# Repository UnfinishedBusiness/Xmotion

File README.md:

# PlasmaTable
CNC Plasma Cutting Table Controls

Build SDL2-2.0.4 with ./configure --disable-video-mir --disable-video-wayland --disable-video-opengl --disable-video-x11 --host=armv7l-raspberry-linux-gnueabihf

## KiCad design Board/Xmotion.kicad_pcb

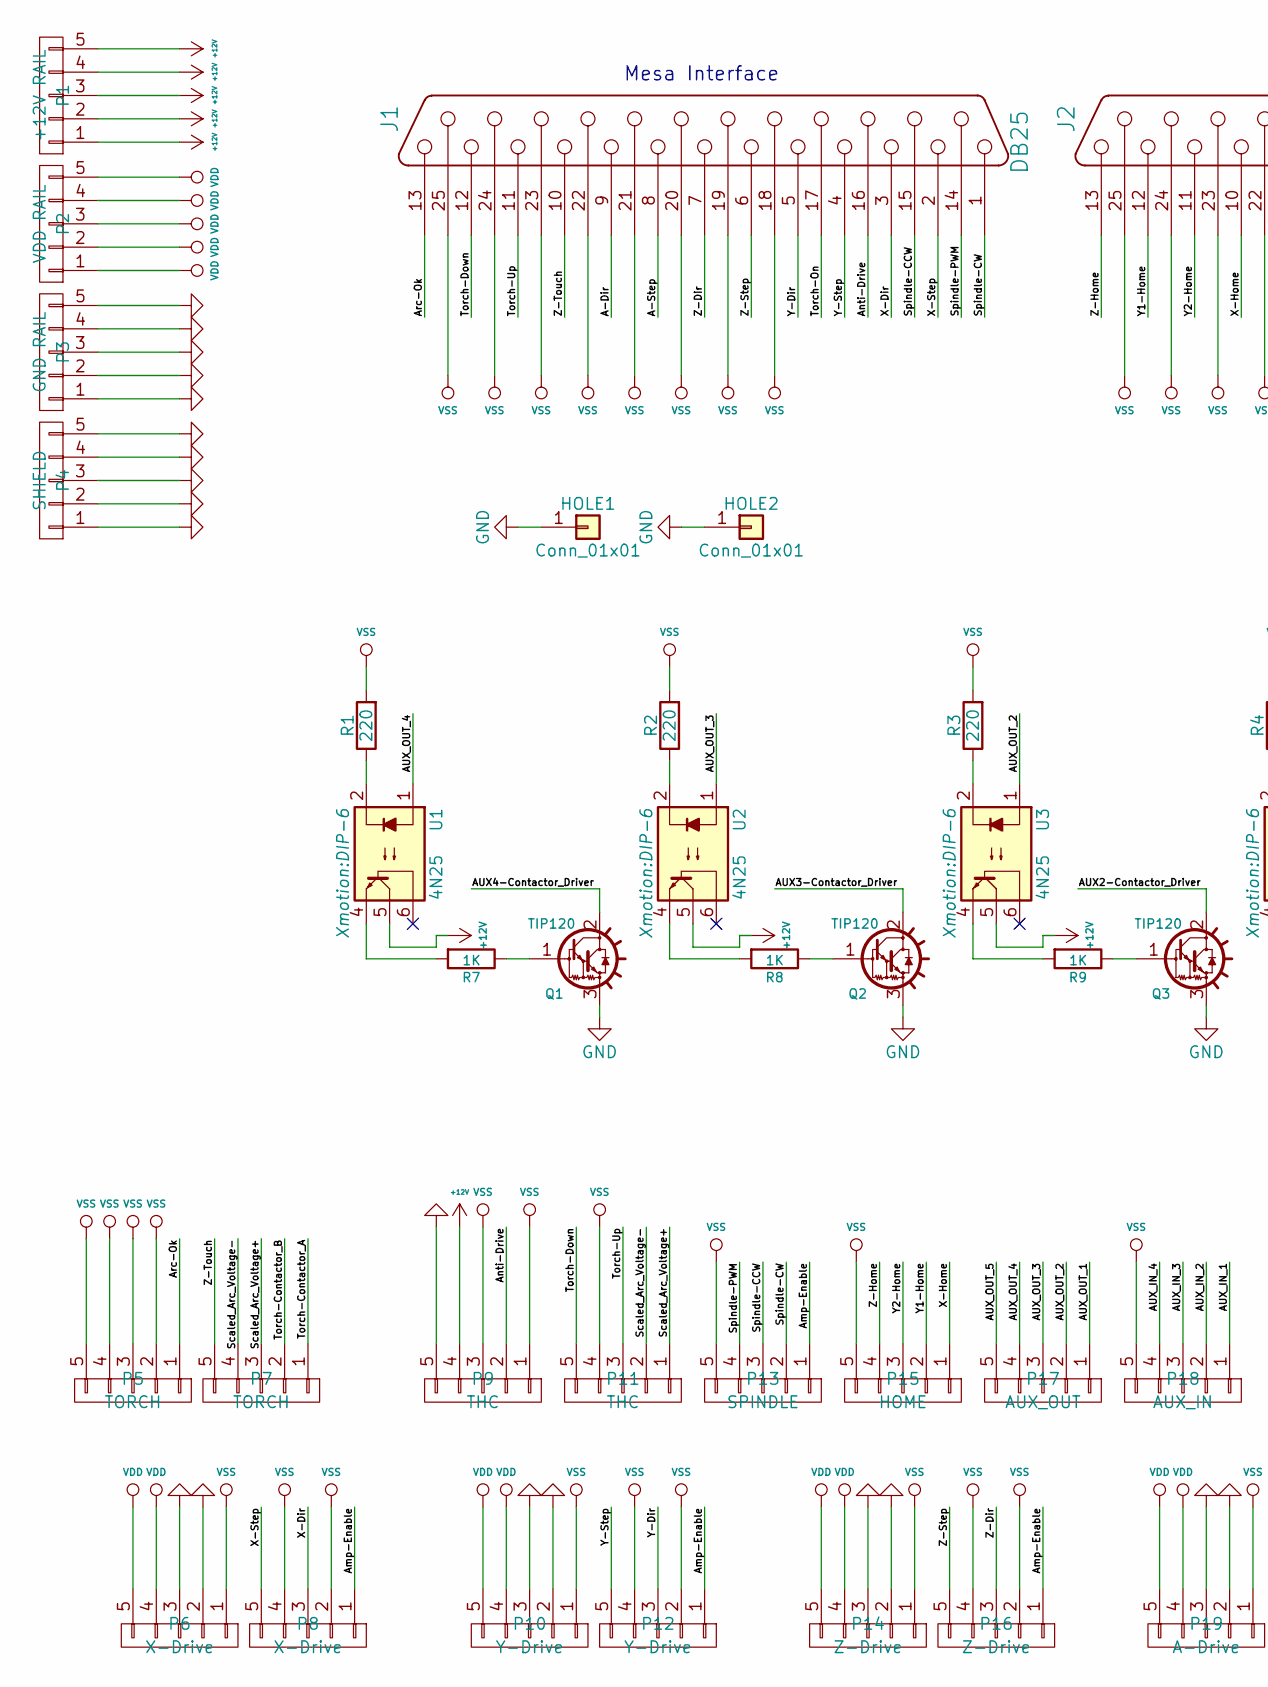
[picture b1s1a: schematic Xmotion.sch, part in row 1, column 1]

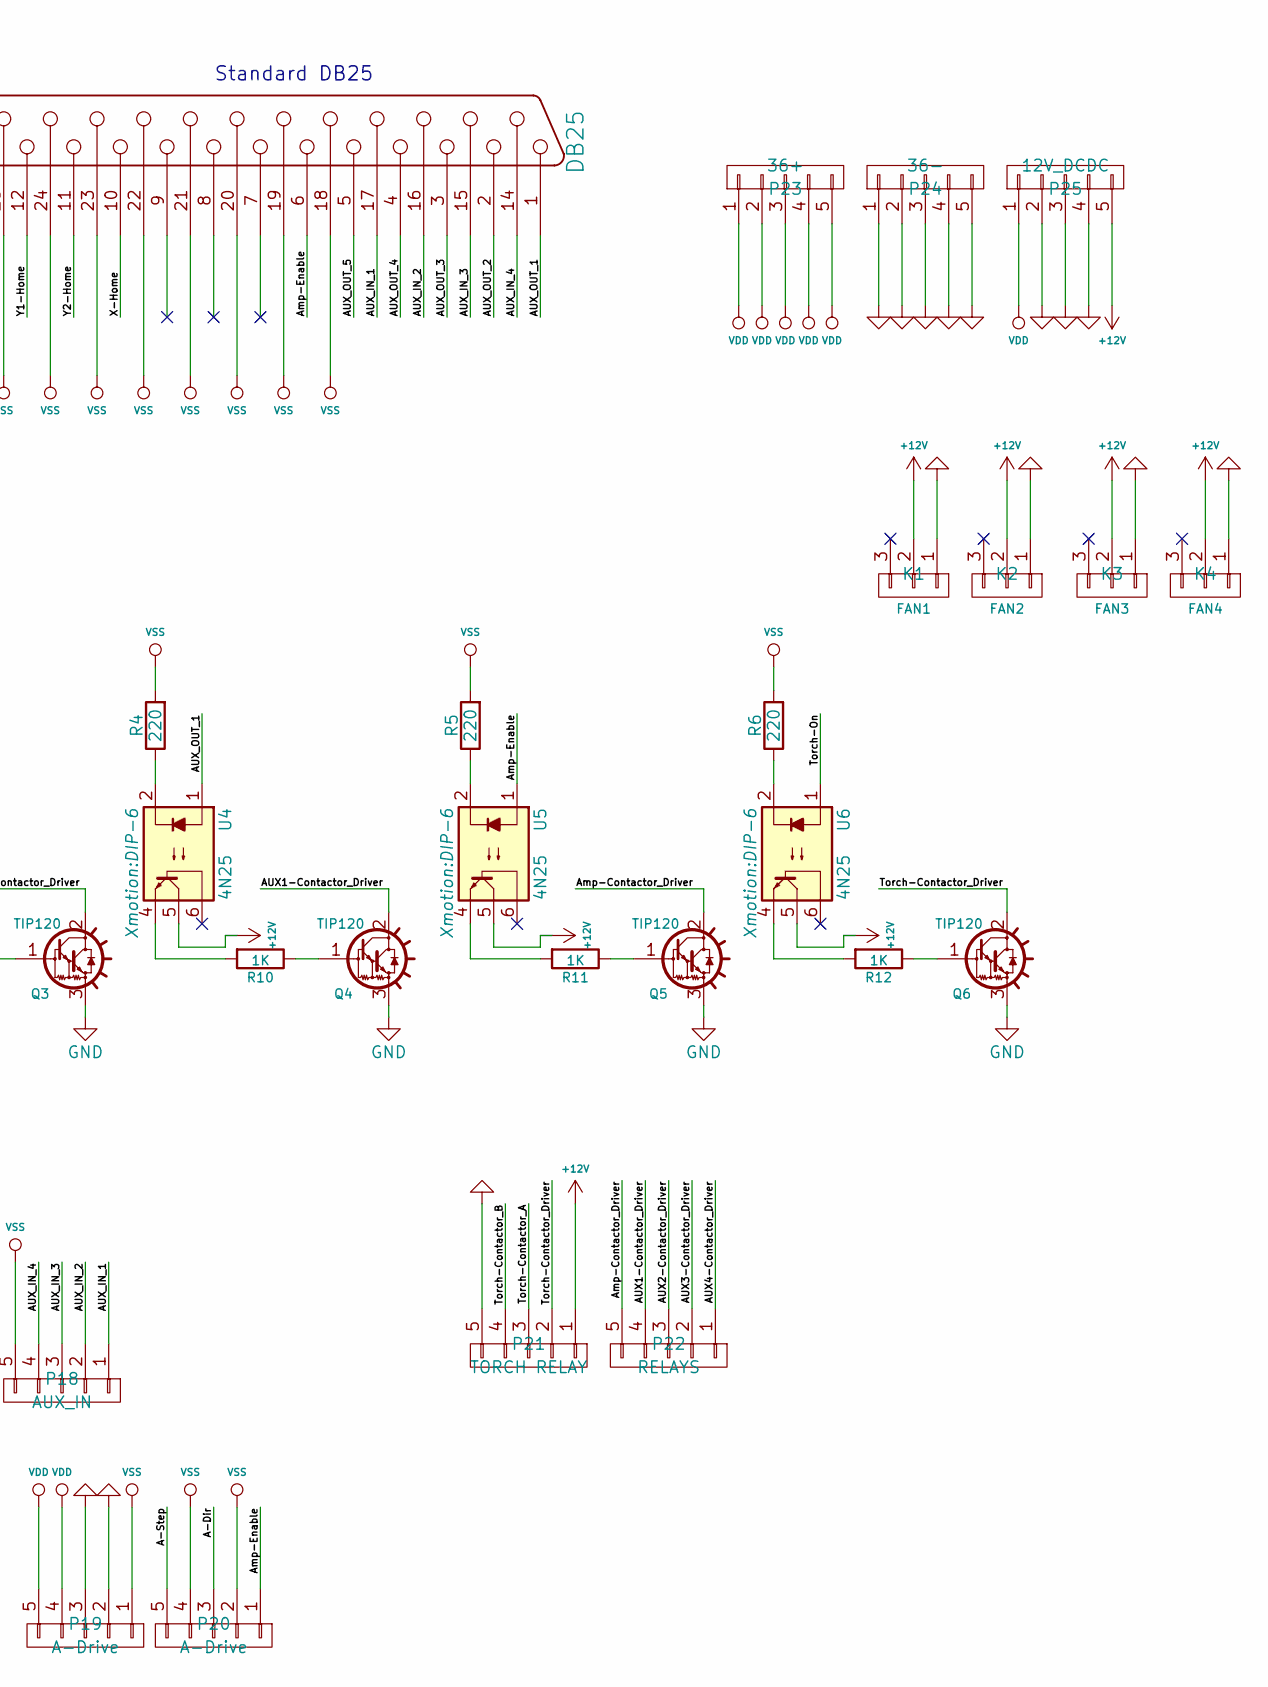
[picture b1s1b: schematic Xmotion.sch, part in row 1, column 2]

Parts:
HOLE1, HOLE2: Conn_01x01; BOLT_HOLE
J1, J2: DB25; DB25MC
K1: FAN1; SIL-3
K2: FAN2; SIL-3
K3: FAN3; SIL-3
K4: FAN4; SIL-3
P1: +12V RAIL; PLUGABLE_HEADER
P2: VDD RAIL; PLUGABLE_HEADER
P3: GND RAIL; PLUGABLE_HEADER
P4: SHIELD; PLUGABLE_HEADER
P5, P7: TORCH; PLUGABLE_HEADER
P6, P8: X-Drive; PLUGABLE_HEADER
P9, P11: THC; PLUGABLE_HEADER
P10, P12: Y-Drive; PLUGABLE_HEADER
P13: SPINDLE; PLUGABLE_HEADER
P14, P16: Z-Drive; PLUGABLE_HEADER
P15: HOME; PLUGABLE_HEADER
P17: AUX_OUT; PLUGABLE_HEADER
P18: AUX_IN; PLUGABLE_HEADER
P19, P20: A-Drive; PLUGABLE_HEADER
P21: TORCH RELAY; PLUGABLE_HEADER
P22: RELAYS; PLUGABLE_HEADER
P23: 36+; PLUGABLE_HEADER
P24: 36-; PLUGABLE_HEADER
P25: 12V_DCDC; PLUGABLE_HEADER
Q1, Q2, Q3, Q4, Q5, Q6: TIP120; TO220
R1, R2, R3, R4, R5, R6: 220; R3
R7, R8, R9, R10, R11, R12: 1K; R3
U1, U2, U3, U4, U5, U6: 4N25; DIP-6

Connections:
+12V: K1.2, K2.2, K3.2, K4.2, P1.1, P1.2, P1.3, P1.4, P1.5, P9.4, P21.1, P25.5, U1.5, U2.5, U3.5, U4.5, U5.5, U6.5
/A-Dir: J1.9, P20.3
/A-Step: J1.8, P20.5
/AUX1-Contactor_Driver: P22.4, Q4.2 (C)
/AUX2-Contactor_Driver: P22.3, Q3.2 (C)
/AUX3-Contactor_Driver: P22.2, Q2.2 (C)
/AUX4-Contactor_Driver: P22.1, Q1.2 (C)
/AUX_IN_1: J2.17, P18.1
/AUX_IN_2: J2.16, P18.2
/AUX_IN_3: J2.15, P18.3
/AUX_IN_4: J2.14, P18.4
/AUX_OUT_1: J2.1, P17.1, U4.1
/AUX_OUT_2: J2.2, P17.2, U3.1
/AUX_OUT_3: J2.3, P17.3, U2.1
/AUX_OUT_4: J2.4, P17.4, U1.1
/AUX_OUT_5: J2.5, P17.5
/Amp-Contactor_Driver: P22.5, Q5.2 (C)
/Amp-Enable: J2.6, P8.1, P12.1, P13.1, P16.1, P20.1, U5.1
/Anti-Drive: J1.16, P9.2
/Arc-Ok: J1.13, P5.1
/Scaled_Arc_Voltage+: P7.3, P11.1
/Scaled_Arc_Voltage-: P7.4, P11.2
/Spindle-CCW: J1.15, P13.3
/Spindle-CW: J1.1, P13.2
/Spindle-PWM: J1.14, P13.4
/Torch-Contactor_A: P7.1, P21.3
/Torch-Contactor_B: P7.2, P21.4
/Torch-Contactor_Driver: P21.2, Q6.2 (C)
/Torch-Down: J1.12, P11.5
/Torch-On: J1.17, U6.1
/Torch-Up: J1.11, P11.3
/X-Dir: J1.3, P8.3
/X-Home: J2.10, P15.1
/X-Step: J1.2, P8.5
/Y1-Home: J2.12, P15.2
/Y2-Home: J2.11, P15.3
/Y-Dir: J1.5, P12.3
/Y-Step: J1.4, P12.5
/Z-Dir: J1.7, P16.3
/Z-Home: J2.13, P15.4
/Z-Step: J1.6, P16.5
/Z-Touch: J1.10, P7.5
GND: HOLE1.1, HOLE2.1, K1.1, K2.1, K3.1, K4.1, P3.1, P3.2, P3.3, P3.4, P3.5, P4.1, P4.2, P4.3, P4.4, P4.5, P6.2, P6.3, P9.5, P10.2, P10.3, P14.2, P14.3, P19.2, P19.3, P21.5, P24.1, P24.2, P24.3, P24.4, P24.5, P25.2, P25.3, P25.4, Q1.3 (E), Q2.3 (E), Q3.3 (E), Q4.3 (E), Q5.3 (E), Q6.3 (E)
unnamed: Q1.1 (B), R7.1
unnamed: Q2.1 (B), R8.1
unnamed: Q3.1 (B), R9.1
unnamed: Q4.1 (B), R10.1
unnamed: Q5.1 (B), R11.1
unnamed: Q6.1 (B), R12.1
unnamed: R1.1, U1.2
unnamed: R2.1, U2.2
unnamed: R3.1, U3.2
unnamed: R4.1, U4.2
unnamed: R5.1, U5.2
unnamed: R6.1, U6.2
unnamed: R7.2, U1.4
unnamed: R8.2, U2.4
unnamed: R9.2, U3.4
unnamed: R10.2, U4.4
unnamed: R11.2, U5.4
unnamed: R12.2, U6.4
VDD: P2.1, P2.2, P2.3, P2.4, P2.5, P6.4, P6.5, P10.4, P10.5, P14.4, P14.5, P19.4, P19.5, P23.1, P23.2, P23.3, P23.4, P23.5, P25.1
VSS: J1.18, J1.19, J1.20, J1.21, J1.22, J1.23, J1.24, J1.25, J2.18, J2.19, J2.20, J2.21, J2.22, J2.23, J2.24, J2.25, P5.2, P5.3, P5.4, P5.5, P6.1, P8.2, P8.4, P9.1, P9.3, P10.1, P11.4, P12.2, P12.4, P13.5, P14.1, P15.5, P16.2, P16.4, P18.5, P19.1, P20.2, P20.4, R1.2, R2.2, R3.2, R4.2, R5.2, R6.2

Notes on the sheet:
Mesa Interface
Standard DB25

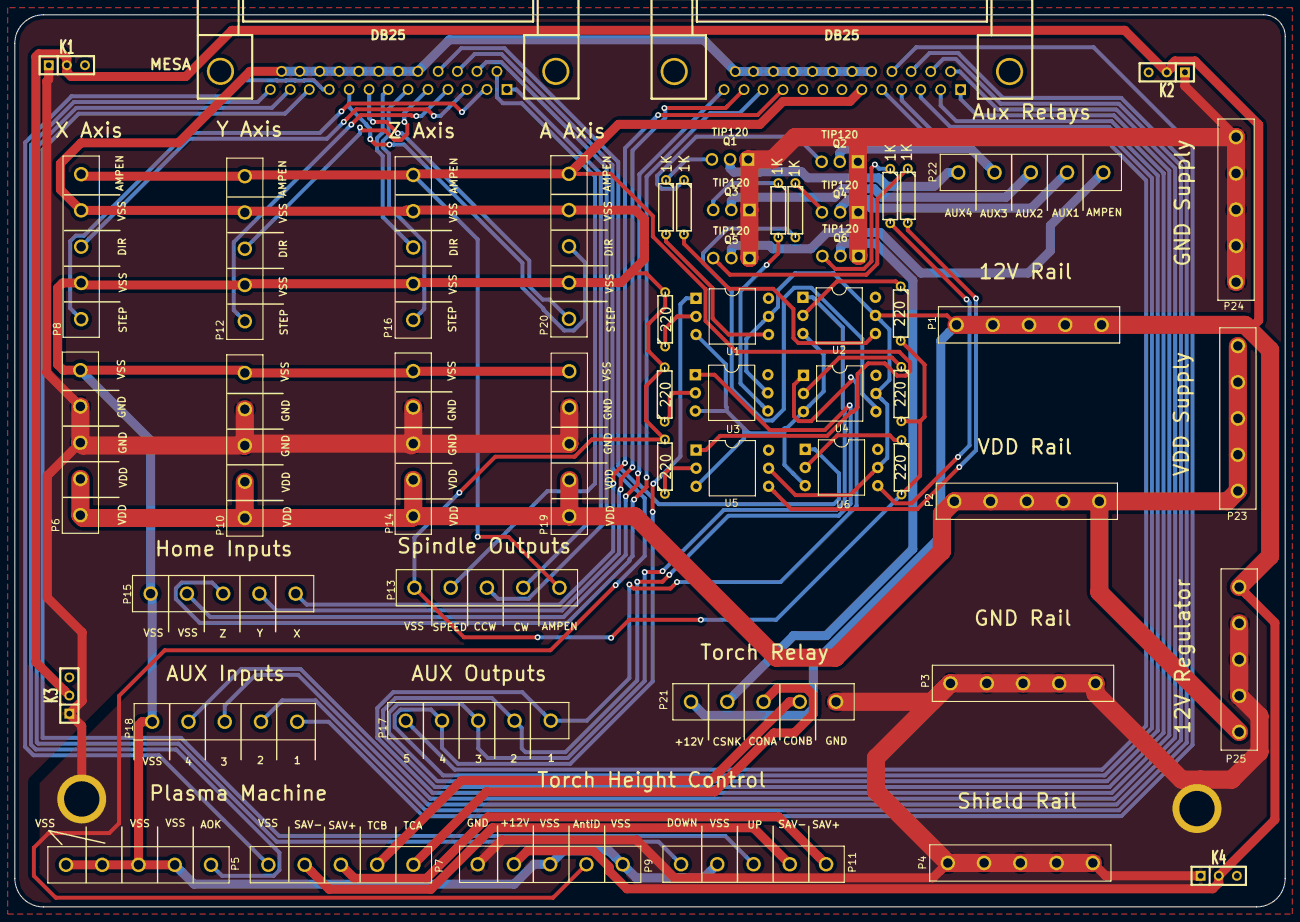
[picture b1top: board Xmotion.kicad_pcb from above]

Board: 2 copper layers, 178.0 x 125.0 mm, 57 parts (0 on the bottom side), 63 nets.

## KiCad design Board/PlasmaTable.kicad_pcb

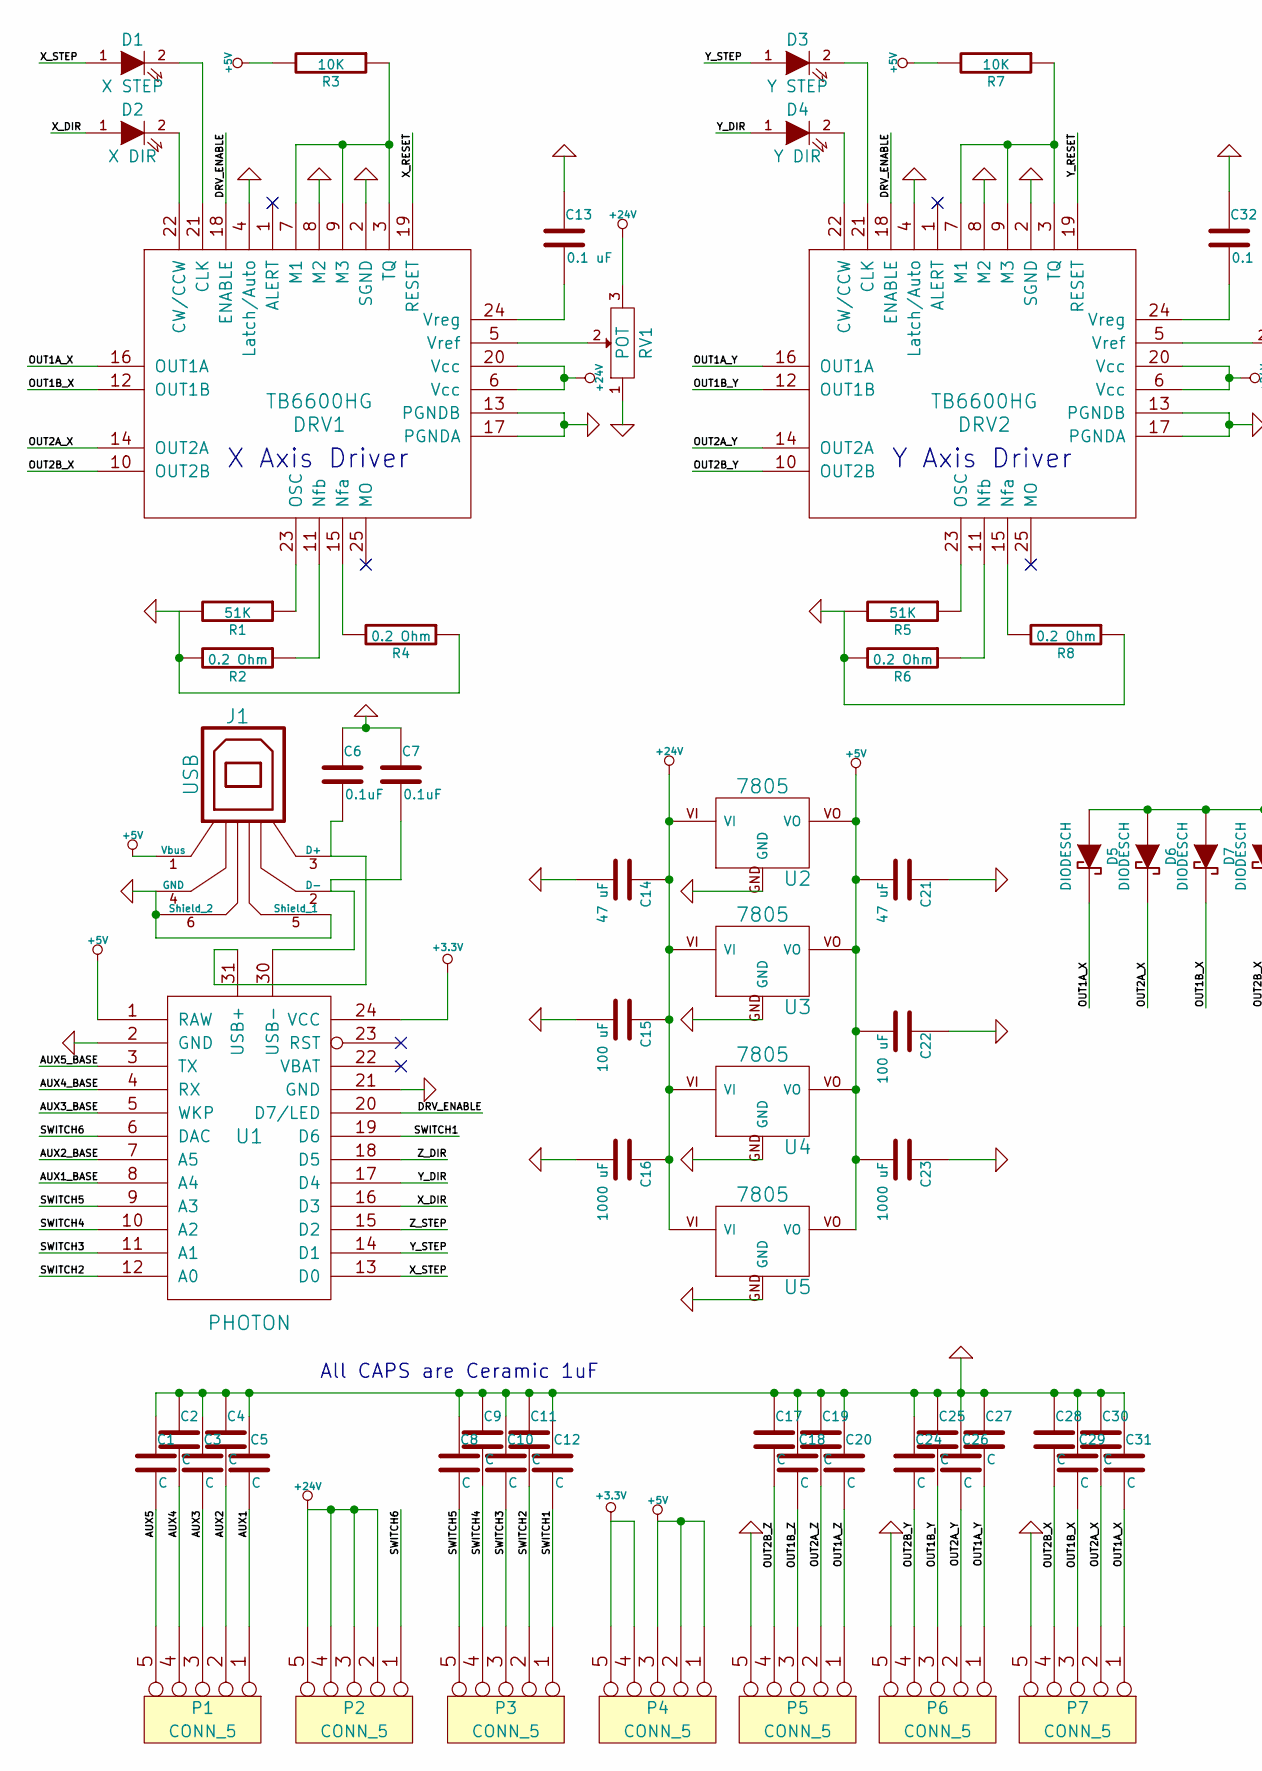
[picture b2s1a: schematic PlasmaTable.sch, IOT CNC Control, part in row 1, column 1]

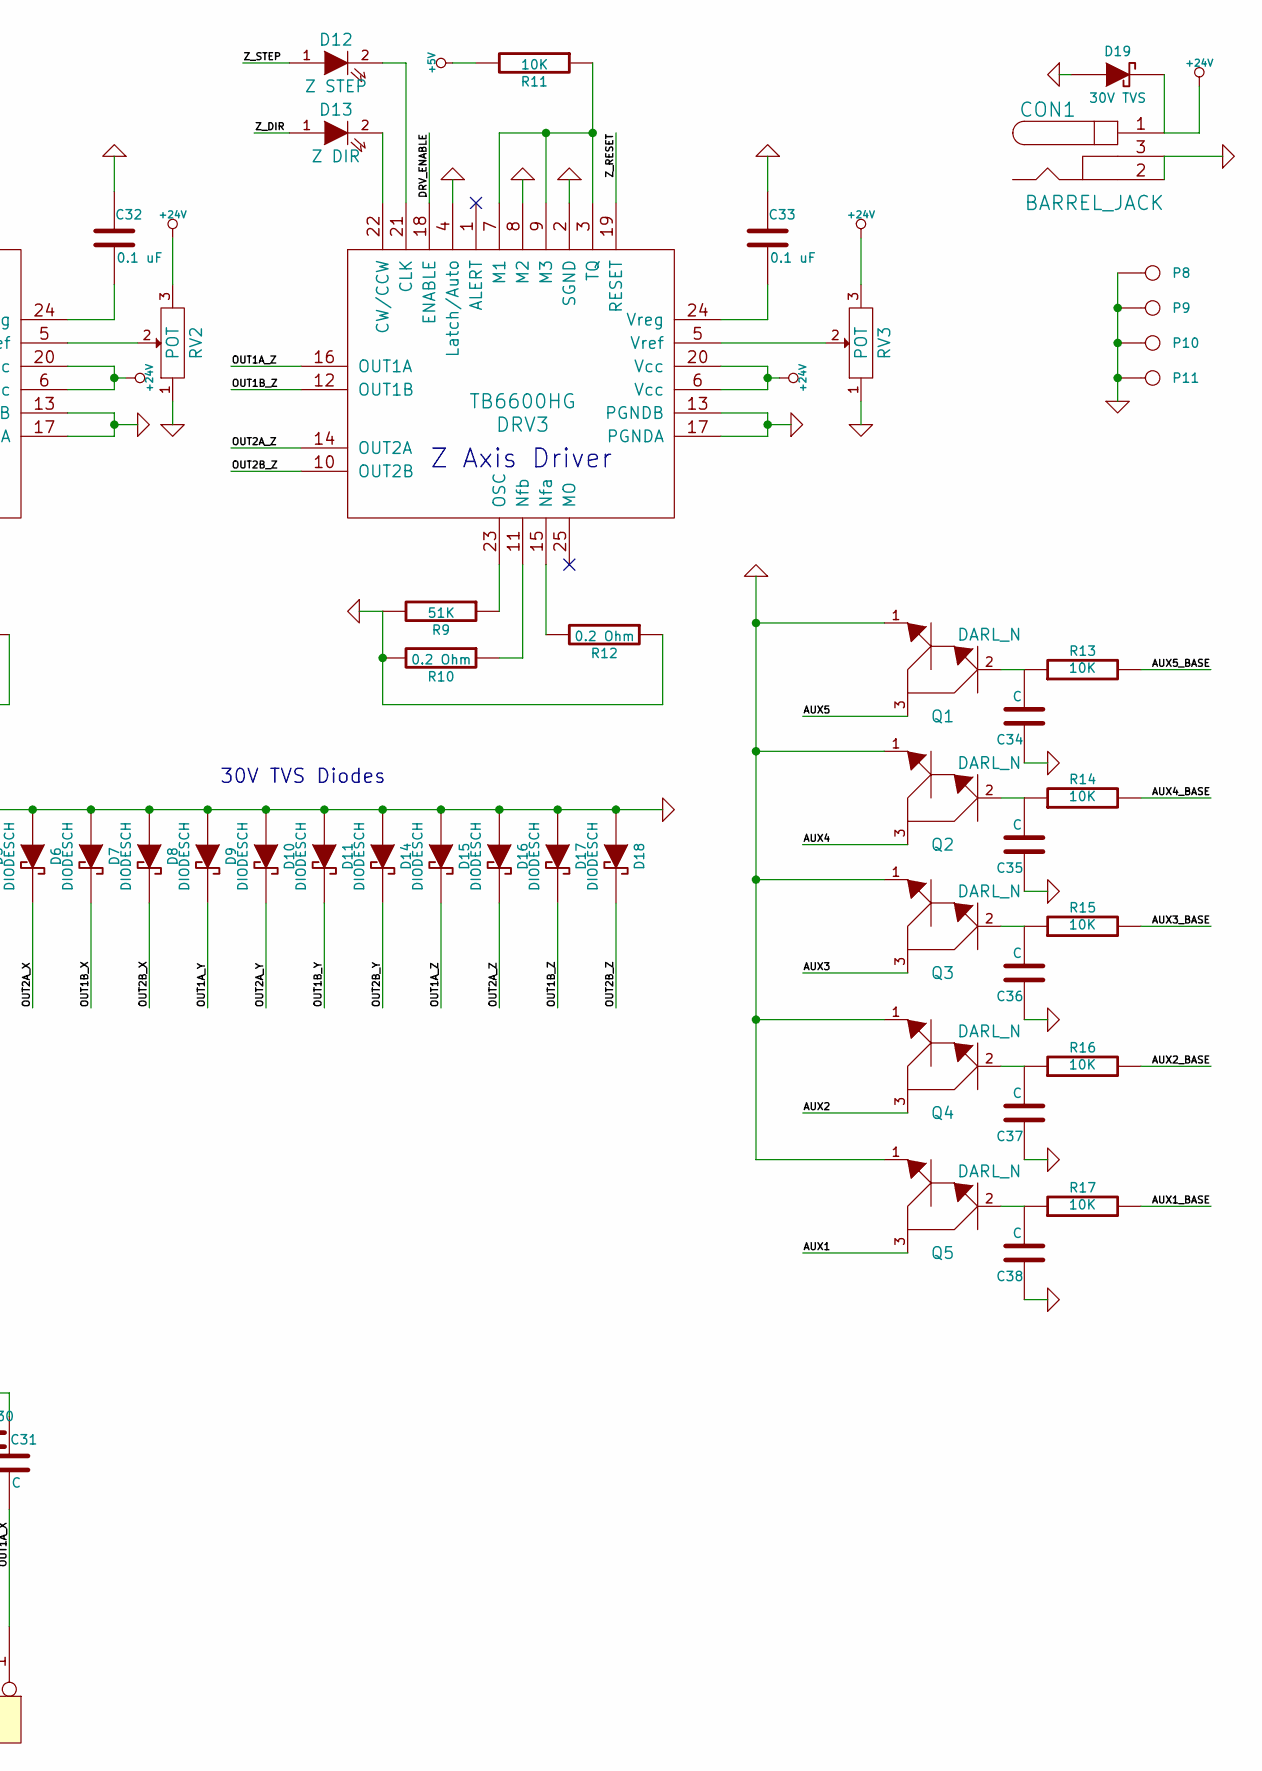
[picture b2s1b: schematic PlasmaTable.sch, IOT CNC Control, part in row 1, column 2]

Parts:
C1, C2, C3, C4, C5, C8, C9, C10, C11, C12, C17, C18, C19, C20, C24, C25, C26, C27, C28, C29, C30, C31, C34, C35, C36, C37, C38: C; c_0603
C6, C7: 0.1uF; c_0603
C13, C32, C33: 0.1 uF; c_0603
C14, C21: 47 uF; c_0603
C15, C22: 100 uF; c_0603
C16, C23: 1000 uF; c_0603
CON1: BARREL_JACK
D1: X STEP; Led_1206
D2: X DIR; Led_1206
D3: Y STEP; Led_1206
D4: Y DIR; Led_1206
D5, D6, D7, D8, D9, D10, D11, D14, D15, D16, D17, D18: DIODESCH; Led_1206
D12: Z STEP; Led_1206
D13: Z DIR; Led_1206
D19: 30V TVS; Led_1206
DRV1, DRV2, DRV3: TB6600HG; hzip25-100f
J1: USB; USB_B
P1, P2, P3, P4, P5, P6, P7: CONN_5; SIL-5
P8, P9, P10, P11: CONN_1; BOLT_HOLE
Q1, Q2, Q3, Q4, Q5: DARL_N; TO-252-3
R1, R5, R9: 51K; r_2010
R2, R4, R6, R8, R10, R12: 0.2 Ohm; r_2010
R3, R7, R11, R13, R14, R15, R16, R17: 10K; r_2010
RV1, RV2, RV3: POT; TRIM_POT
U1: PHOTON; Spark-PHOTON_SMD
U2, U3, U4, U5: 7805; 7805_DPAK

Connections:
+3.3V: P4.4, P4.5, U1.24 (VCC)
+5V: C21.2, C22.2, C23.2, J1.1 (Vbus), P4.1, P4.2, P4.3, R3.2, R7.2, R11.2, U1.1 (RAW), U2.VO, U3.VO, U4.VO, U5.VO
+24V: C14.1, C15.1, C16.1, CON1.1, D19.2 (K), DRV1.6 (Vcc), DRV1.20 (Vcc), DRV2.6 (Vcc), DRV2.20 (Vcc), DRV3.6 (Vcc), DRV3.20 (Vcc), P2.2, P2.3, P2.4, P2.5, RV1.3, RV2.3, RV3.3, U2.VI, U3.VI, U4.VI, U5.VI
/AUX1: C5.2, P1.1, Q5.3
/AUX1_BASE: R17.2, U1.8 (A4)
/AUX2: C4.2, P1.2, Q4.3
/AUX2_BASE: R16.2, U1.7 (A5)
/AUX3: C3.2, P1.3, Q3.3
/AUX3_BASE: R15.2, U1.5 (WKP)
/AUX4: C2.2, P1.4, Q2.3
/AUX4_BASE: R14.2, U1.4 (RX)
/AUX5: C1.2, P1.5, Q1.3
/AUX5_BASE: R13.2, U1.3 (TX)
/DRV_ENABLE: DRV1.18 (ENABLE), DRV2.18 (ENABLE), DRV3.18 (ENABLE), U1.20 (D7/LED)
/OUT1A_X: C31.2, D5.2 (K), DRV1.16 (OUT1A), P7.1
/OUT1A_Y: C27.2, D9.2 (K), DRV2.16 (OUT1A), P6.1
/OUT1A_Z: C20.2, D15.2 (K), DRV3.16 (OUT1A), P5.1
/OUT1B_X: C29.2, D7.2 (K), DRV1.12 (OUT1B), P7.3
/OUT1B_Y: C25.2, D11.2 (K), DRV2.12 (OUT1B), P6.3
/OUT1B_Z: C18.2, D17.2 (K), DRV3.12 (OUT1B), P5.3
/OUT2A_X: C30.2, D6.2 (K), DRV1.14 (OUT2A), P7.2
/OUT2A_Y: C26.2, D10.2 (K), DRV2.14 (OUT2A), P6.2
/OUT2A_Z: C19.2, D16.2 (K), DRV3.14 (OUT2A), P5.2
/OUT2B_X: C28.2, D8.2 (K), DRV1.10 (OUT2B), P7.4
/OUT2B_Y: C24.2, D14.2 (K), DRV2.10 (OUT2B), P6.4
/OUT2B_Z: C17.2, D18.2 (K), DRV3.10 (OUT2B), P5.4
/SWITCH1: C12.2, P3.1, U1.19 (D6)
/SWITCH2: C11.2, P3.2, U1.12 (A0)
/SWITCH3: C10.2, P3.3, U1.11 (A1)
/SWITCH4: C9.2, P3.4, U1.10 (A2)
/SWITCH5: C8.2, P3.5, U1.9 (A3)
/SWITCH6: P2.1, U1.6 (DAC)
/X_DIR: D2.1 (A), U1.16 (D3)
/X_STEP: D1.1 (A), U1.13 (D0)
/Y_DIR: D4.1 (A), U1.17 (D4)
/Y_STEP: D3.1 (A), U1.14 (D1)
/Z_DIR: D13.1 (A), U1.18 (D5)
/Z_STEP: D12.1 (A), U1.15 (D2)
GND: C1.1, C2.1, C3.1, C4.1, C5.1, C6.1, C7.1, C8.1, C9.1, C10.1, C11.1, C12.1, C13.1, C14.2, C15.2, C16.2, C17.1, C18.1, C19.1, C20.1, C21.1, C22.1, C23.1, C24.1, C25.1, C26.1, C27.1, C28.1, C29.1, C30.1, C31.1, C32.1, C33.1, C34.1, C35.1, C36.1, C37.1, C38.1, CON1.2, CON1.3, D5.1 (A), D6.1 (A), D7.1 (A), D8.1 (A), D9.1 (A), D10.1 (A), D11.1 (A), D14.1 (A), D15.1 (A), D16.1 (A), D17.1 (A), D18.1 (A), D19.1 (A), DRV1.2 (SGND), DRV1.4 (Latch/Auto), DRV1.8 (M2), DRV1.13 (PGNDB), DRV1.17 (PGNDA), DRV2.2 (SGND), DRV2.4 (Latch/Auto), DRV2.8 (M2), DRV2.13 (PGNDB), DRV2.17 (PGNDA), DRV3.2 (SGND), DRV3.4 (Latch/Auto), DRV3.8 (M2), DRV3.13 (PGNDB), DRV3.17 (PGNDA), J1.4 (GND), J1.5 (Shield_1), J1.6 (Shield_2), P5.5, P6.5, P7.5, P8.1, P9.1, P10.1, P11.1, Q1.1, Q2.1, Q3.1, Q4.1, Q5.1, R1.2, R2.2, R4.1, R5.2, R6.2, R8.1, R9.2, R10.2, R12.1, RV1.1, RV2.1, RV3.1, U1.2 (GND), U1.21 (GND), U2.GND, U3.GND, U4.GND, U5.GND
unnamed: C6.2, J1.3 (D+), U1.31 (USB+)
unnamed: C7.2, J1.2 (D-), U1.30 (USB-)
unnamed: C13.2, DRV1.24 (Vreg)
unnamed: C32.2, DRV2.24 (Vreg)
unnamed: C33.2, DRV3.24 (Vreg)
unnamed: C34.2, Q1.2, R13.1
unnamed: C35.2, Q2.2, R14.1
unnamed: C36.2, Q3.2, R15.1
unnamed: C37.2, Q4.2, R16.1
unnamed: C38.2, Q5.2, R17.1
unnamed: D1.2 (K), DRV1.21 (CLK)
unnamed: D2.2 (K), DRV1.22 (CW/CCW)
unnamed: D3.2 (K), DRV2.21 (CLK)
unnamed: D4.2 (K), DRV2.22 (CW/CCW)
unnamed: D12.2 (K), DRV3.21 (CLK)
unnamed: D13.2 (K), DRV3.22 (CW/CCW)
unnamed: DRV1.3 (TQ), DRV1.7 (M1), DRV1.9 (M3), R3.1
unnamed: DRV1.5 (Vref), RV1.2
unnamed: DRV1.11 (Nfb), R2.1
unnamed: DRV1.15 (Nfa), R4.2
unnamed: DRV1.23 (OSC), R1.1
unnamed: DRV2.3 (TQ), DRV2.7 (M1), DRV2.9 (M3), R7.1
unnamed: DRV2.5 (Vref), RV2.2
unnamed: DRV2.11 (Nfb), R6.1
unnamed: DRV2.15 (Nfa), R8.2
unnamed: DRV2.23 (OSC), R5.1
unnamed: DRV3.3 (TQ), DRV3.7 (M1), DRV3.9 (M3), R11.1
unnamed: DRV3.5 (Vref), RV3.2
unnamed: DRV3.11 (Nfb), R10.1
unnamed: DRV3.15 (Nfa), R12.2
unnamed: DRV3.23 (OSC), R9.1

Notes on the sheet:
X Axis Driver
Y Axis Driver
Z Axis Driver
All CAPS are Ceramic 1uF
30V TVS Diodes

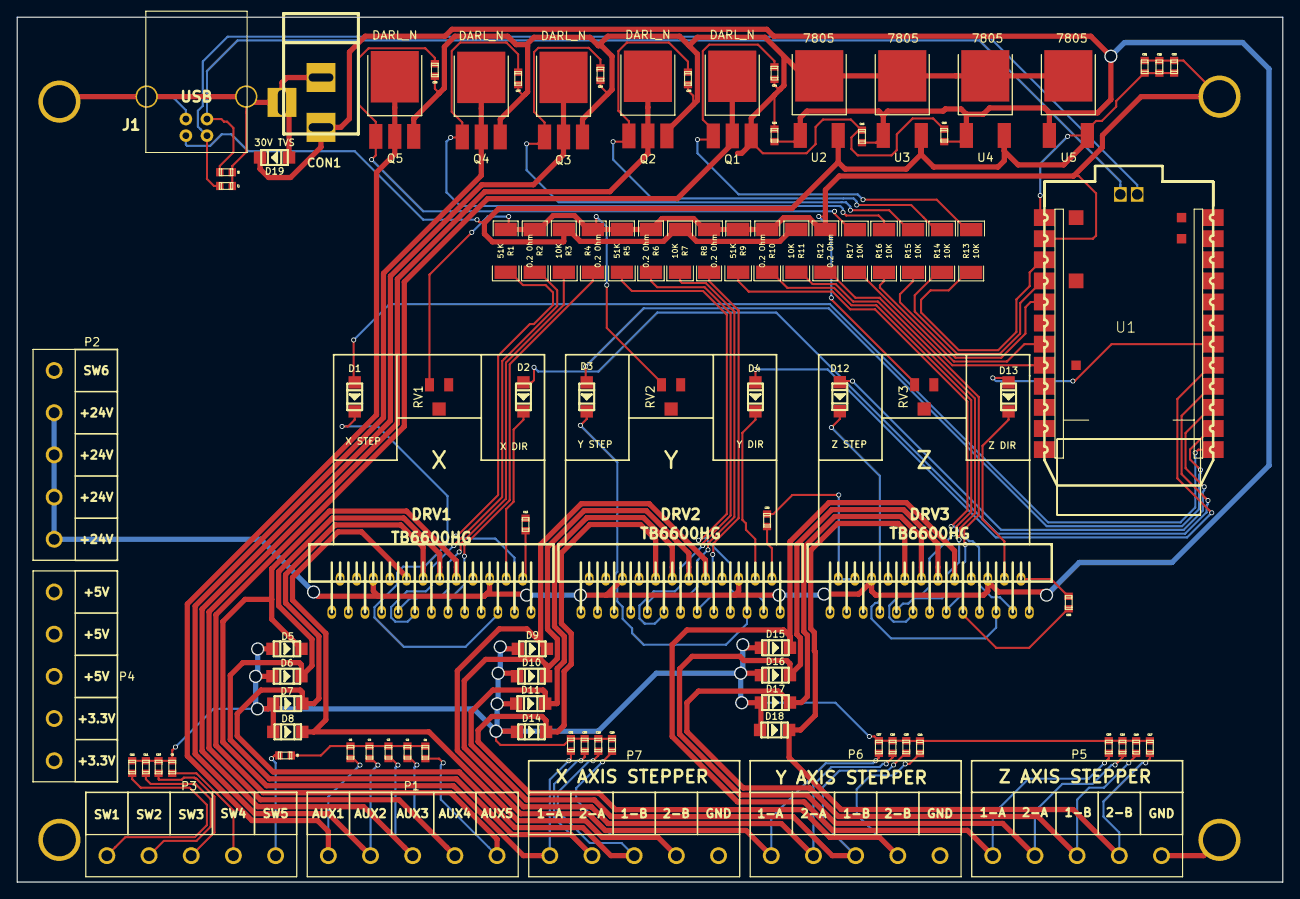
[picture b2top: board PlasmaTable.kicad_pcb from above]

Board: 2 copper layers, 152.4 x 104.1 mm, 103 parts (0 on the bottom side), 70 nets.

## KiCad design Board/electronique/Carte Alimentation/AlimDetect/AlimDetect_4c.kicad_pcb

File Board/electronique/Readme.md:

# electronique
Les schémas des cartes électroniques utilisées dans nos robots

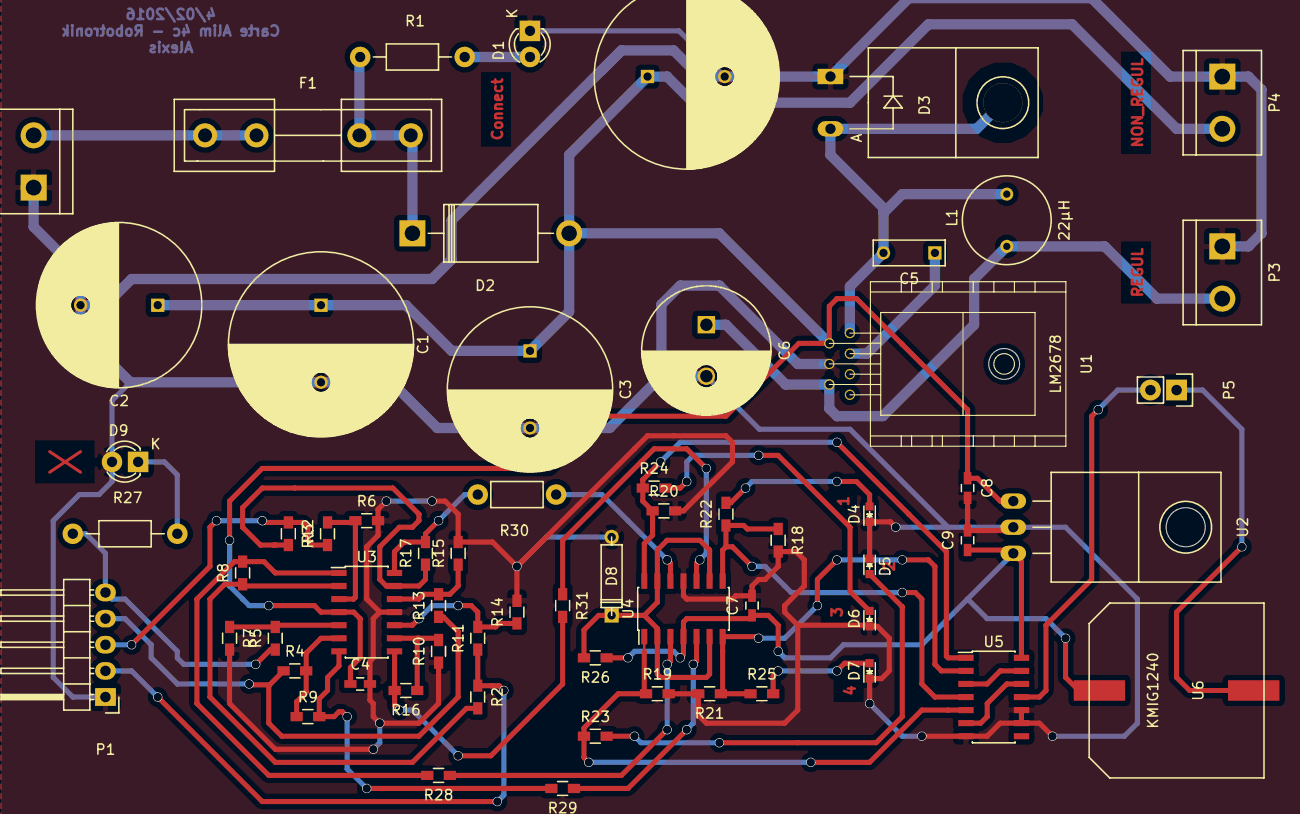
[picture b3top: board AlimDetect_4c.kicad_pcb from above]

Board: 2 copper layers, 63 parts (0 on the bottom side), 43 nets.

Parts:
C1: 820µF; C_Radial_D18_L36_P7.5
C2, C3: 680µF; C_Radial_D16_L25_P7.5
C4, C7: 100n; C_0603_HandSoldering
C5: 0.01µF; C_Rect_L7_W2.5_P5
C6: 820µF; C_Radial_D12.5_L25_P5
C8: 0.33µ; C_0603_HandSoldering
C9: 0.1µ; C_0603_HandSoldering
C10: 1200µF; C_Radial_D18_L36_P7.5
D1, D9: LED; LED-3MM
D2: 1N5404; Diode_DO-201AD_Horizontal_RM15
D3: DIODESCH; Diode_TO-220_Horizontal
D4, D5, D6, D7: LED; LED_0603
D8: 1N746A; D3
F1: F8AL250/SCHURTER 0031.8201; Fuseholder5x20_horiz_open_inline_Type-I
L1: 22µH; Coil_Trough_Hole
P1: CONN_01X05; Pin_Header_Angled_1x05
P2, P3, P4: CONN_01X02; bornier2
P5: CONN_01X02; Pin_Header_Straight_1x02
R1: 680; Resistor_Horizontal_RM10mm
R2, R3, R4, R5, R6, R7, R8, R9, R10, R11, R12, R13, R14, R15, R16, R17: R; R_0603_HandSoldering
R18, R19, R20, R21: 15k; R_0603_HandSoldering
R22, R23, R24, R25: 150; R_0603_HandSoldering
R26: 82; R_0603_HandSoldering
R27: 820; Resistor_Horizontal_RM10mm
R28, R29, R31: 510; R_0603_HandSoldering
R30: 510; Resistor_Horizontal_RM7mm
U1: LM2678; to220-7-horiz_5772
U2: 7805_correctPin; TO-220_Neutral123_Horizontal
U3, U4: TLC274; SOIC-14_3.9x8.7mm_Pitch1.27mm
U5: 74LS08; SOIC-14_3.9x8.7mm_Pitch1.27mm
U6: KMIG1240; kmig1240

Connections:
+5V: C7.1, C9.1, R26.1, U2.3, U4.4, U5.14, U6.1
/PWR_redressé: C1.1, C2.1, C3.1, C4.1, C8.1, C10.1, D2.2, P4.2, U1.2, U2.1, U3.4
/Vref: D8.1, R26.2, U4.2, U4.6, U4.9, U4.13
GND: C1.2, C2.2, C3.2, C4.2, C6.2, C7.2, C8.2, C9.2, C10.2, D1.1, D3.1, D4.1, D5.1, D6.1, D7.1, D8.2, D9.2, P1.1, P2.1, P3.1, P4.1, R6.2, R7.2, R10.1, R14.2, R15.2, R18.2, R19.2, R20.2, R21.2, U1.4, U2.2, U3.11, U4.11, U5.7, U5.9, U5.10
unnamed: C5.1, U1.3
unnamed: C5.2, D3.2, L1.1, U1.1
unnamed: C6.1, L1.2, P3.2, U1.6
unnamed: D1.2, R1.2
unnamed: D2.1, F1.2, R1.1
unnamed: D4.2, R22.2
unnamed: D5.2, R23.2
unnamed: D6.2, R24.2
unnamed: D7.2, R25.2
unnamed: D9.1, R27.2
unnamed: F1.1, P2.2
unnamed: P1.2, R2.1, R11.1
unnamed: P1.3, R3.1, R12.1
unnamed: P1.4, R4.1, R13.1
unnamed: P1.5, R5.1, R27.1
unnamed: P5.1, U6.2
unnamed: P5.2, U5.11
unnamed: R2.2, R8.1, U3.2
unnamed: R3.2, R6.1, U3.3
unnamed: R4.2, R9.1, U3.6
unnamed: R5.2, R7.1, U3.5
unnamed: R10.2, R16.1, U3.9
unnamed: R11.2, R14.1, U3.10
unnamed: R12.2, R17.1, U3.13
unnamed: R13.2, R15.1, U3.12
unnamed: R16.2, R31.2, U3.8
unnamed: R17.2, R30.2, U3.14
unnamed: R18.1, R22.1, U4.8, U5.4
unnamed: R19.1, R23.1, U4.1, U5.5
unnamed: R20.1, R24.1, U4.14, U5.1
unnamed: R21.1, R25.1, U4.7, U5.2
unnamed: R28.1, U4.3
unnamed: R8.2, R28.2, U3.1
unnamed: R29.1, U4.5
unnamed: R9.2, R29.2, U3.7
unnamed: R30.1, U4.12
unnamed: R31.1, U4.10
unnamed: U5.6, U5.12
unnamed: U5.3, U5.13

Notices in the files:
configs/Xmotion_MainBoard/xmotion.dts:
Copyright 2013
This program is free software; you can redistribute it and/or modify
it under the terms of the GNU General Public License as published by
the Free Software Foundation; either version 2 of the License, or
(at your option) any later version.
